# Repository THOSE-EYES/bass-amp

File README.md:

# A bass guitar preamplifier project

This project features a small, easy-to-use and stable preamplifier for bass guitars. Such preamplifier is meant to be installed inside the bass guitar abd should be connected directly to the output jack.

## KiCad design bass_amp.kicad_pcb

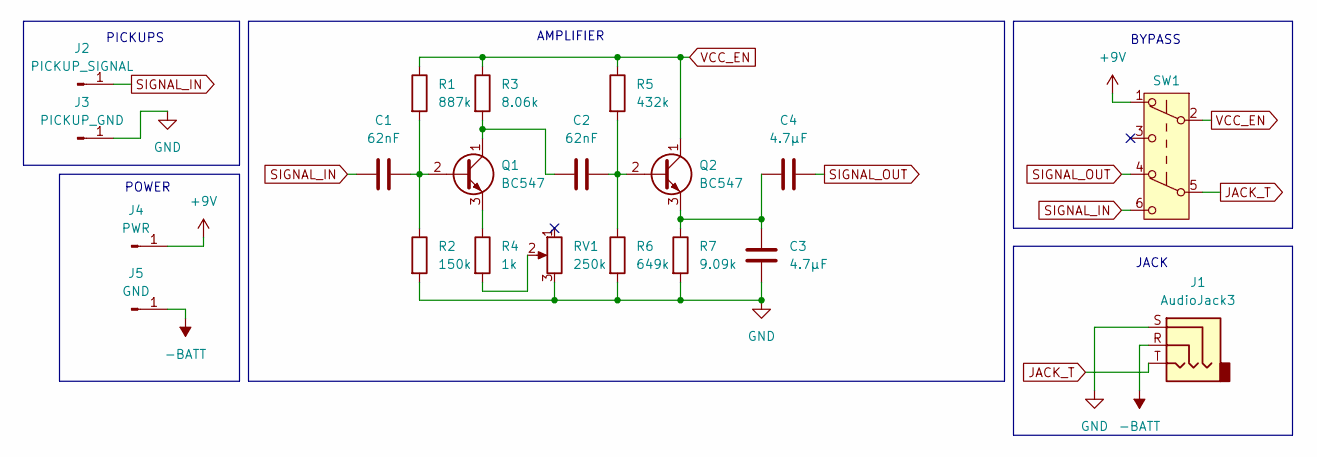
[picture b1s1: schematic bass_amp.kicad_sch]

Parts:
C1, C2: 62nF; C_Disc_D5.1mm_W3.2mm_P5.00mm
C3, C4: 4.7μF; C_Radial_D6.3mm_H7.0mm_P2.50mm
J1: AudioJack3; Custom_Jack_TRS
J2: PICKUP_SIGNAL; SolderWirePad_1x01_SMD_1x2mm
J3: PICKUP_GND; SolderWirePad_1x01_SMD_1x2mm
J4: PWR; SolderWirePad_1x01_SMD_1x2mm
J5: GND; SolderWirePad_1x01_SMD_1x2mm
Q1, Q2: BC547; TO-92_Inline
R1: 887k; R_Axial_DIN0207_L6.3mm_D2.5mm_P7.62mm_Horizontal
R2: 150k; R_Axial_DIN0207_L6.3mm_D2.5mm_P7.62mm_Horizontal
R3: 8.06k; R_Axial_DIN0207_L6.3mm_D2.5mm_P7.62mm_Horizontal
R4: 1k; R_Axial_DIN0207_L6.3mm_D2.5mm_P7.62mm_Horizontal
R5: 432k; R_Axial_DIN0207_L6.3mm_D2.5mm_P7.62mm_Horizontal
R6: 649k; R_Axial_DIN0207_L6.3mm_D2.5mm_P7.62mm_Horizontal
R7: 9.09k; R_Axial_DIN0207_L6.3mm_D2.5mm_P7.62mm_Horizontal
RV1: 250k; Custom_Gain_Potentiometer
SW1: SW_Push_DPDT; SW_CK_JS202011CQN_DPDT_Straight

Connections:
+9V: J4.1, SW1.1 (A)
-BATT: J1.R, J5.1
GND: C3.2, J1.S, J3.1, R2.2, R6.2, R7.2, RV1.3
JACK_T: J1.T, SW1.5 (B)
unnamed: C1.1, Q1.2 (B), R1.2, R2.1
unnamed: C2.2, Q1.1 (C), R3.2
unnamed: Q1.3 (E), R4.1
unnamed: C2.1, Q2.2 (B), R5.2, R6.1
unnamed: C3.1, C4.2, Q2.3 (E), R7.1
unnamed: R4.2, RV1.2
SIGNAL_IN: C1.2, J2.1, SW1.6 (C)
SIGNAL_OUT: C4.1, SW1.4 (A)
VCC_EN: Q2.1 (C), R1.1, R3.1, R5.1, SW1.2 (B)

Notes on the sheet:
BYPASS
POWER
JACK
AMPLIFIER
PICKUPS

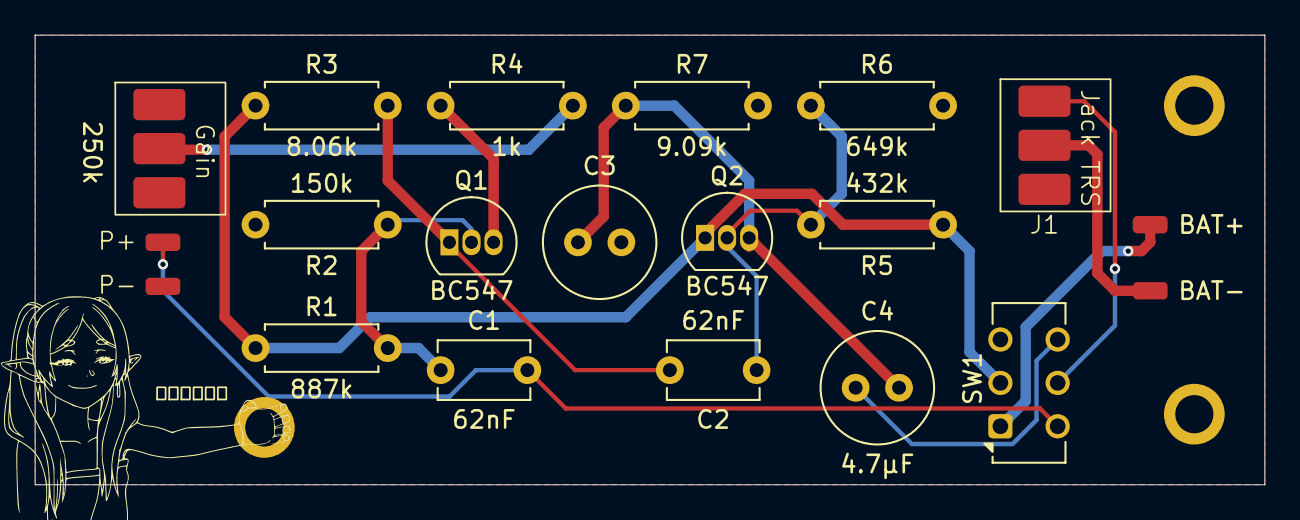
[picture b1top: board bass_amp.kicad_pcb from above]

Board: 2 copper layers, 70.9 x 25.9 mm, 20 parts (0 on the bottom side), 13 nets.

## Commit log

2025-07-12 Initialize the repository
2025-07-12 Upload the schematics of the preamplifier
2025-07-12 Add a potentiometer to change the value of gain
2025-07-12 Add a bypass circuit
2025-07-12 Use standardized values for resistors and capacitors
2025-07-12 Add footprints for the elements
2025-07-12 Add JACK output to the schematics
2025-07-12 Add a footprint for the jack connector
2025-07-12 Add power and signal sources to the schematics
2025-07-12 Rewire the pickups
2025-07-13 Add a PCB project
2025-07-13 Add a custom Frieren logo
2025-07-13 Fill empty PCB zones with GND
2025-07-13 Add a separate library for logos
2025-07-19 Add mounting holes to the PCB
2025-08-02 Fix GND connections and rewire the board's GND traces
2025-08-02 Add info about connectors to the silkscreen
2025-08-02 Add mounting holes and update the logo
